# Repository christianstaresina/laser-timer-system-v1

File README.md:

# Laser Timer System

A portable two-gate laser timing system for sprint and speed training. Gate 1
(transmitter) sends a radio start event when its laser beam breaks. Gate 2
(receiver) starts and stops the timer, shows elapsed time on a 16×2 LCD, and can
display average speed from a configured distance.

v1 hardware is a **single shared PCB**. Role is selected by which v2 sketch is
flashed. There is no in-tree v1 sketch; the active firmware is v2 only.

## Repository layout

| Path | Purpose |
| --- | --- |
| `firmware/transmitter/laser_timer_v2_tx/` | Gate 1 / start-unit Arduino sketch. |
| `firmware/receiver/laser_timer_v2_rx/` | Gate 2 / finish-unit sketch (LCD menu + EEPROM). |
| `firmware/common/radio_protocol_v2.h` | Reference copy of the nRF24 packet contract. Keep in sync with each sketch-local `src/radio_protocol_v2.h`. |
| `hardware/transmitter-or-receiver/` | KiCad 8 source for the shared V1 PCB. |
| `production/transmitter-or-receiver/` | Gerbers, drills, zip, and PCBA BoM. |
| `docs/firmware-v2.md` | Firmware architecture, protocol, workflows, settings, and pitfalls. |
| `docs/hardware-production.md` | Pin map, JST harness pinouts, power tree, expansion headers, and fab artifacts. |
| `docs/Laser_Timer_Schematic.pdf` | Exported schematic. |
| `docs/Laser_Timer_PCBA.jpg` | Assembled board photo. |

Open each v2 sketch **folder** in the Arduino IDE so the adjacent `src/` files
compile with the `.ino`. Sketches include their local `src/radio_protocol_v2.h`;
`firmware/common/` is not on the compile path.

## Quick start

1. Install Arduino IDE (or CLI) with an AVR / Nano board package.
2. Install libraries: `RF24` (TMRh20), `LiquidCrystal_I2C` (plus built-in `SPI`,
   `Wire`, `EEPROM` on the receiver).
3. Board: Arduino Nano / ATmega328P (match the processor variant on the module).
4. Flash `firmware/transmitter/laser_timer_v2_tx/laser_timer_v2_tx.ino` to gate 1.
5. Flash `firmware/receiver/laser_timer_v2_rx/laser_timer_v2_rx.ino` to gate 2.

The buzzer shares Nano UART TX (`D1`). Disconnect the buzzer or expect flaky USB
uploads. Shared hardware assumptions: nRF24 CE `D9` / CSN `D10` / SPI `D11`–`D13`,
beam sensor on `D2` (active `HIGH` when broken), LCD I2C `0x27`. Receiver encoder:
button `D3`, CLK `D4`, DAT `D5`. Both sketches drive `A0` high before radio init;
the PCB maps regulator enable to `A7`. Accessories run on board `+5V` (U1); the
radio runs on board `+3V3` (U2). Those rails are **not** the Nano’s `5V` / `3V3`
pins — see [`docs/hardware-production.md`](docs/hardware-production.md).

## Operating workflow

1. Power the **receiver** first so it is listening (` Pairing...` /
   `Waiting for link`).
2. Power the transmitter. `setup()` blocks in `waitForPairing()` until
   `sendPacket(CMD_PING)` returns true, then listens for finish packets.
3. Confirm the receiver leaves pairing (it accepts **any** valid magic packet,
   not only pings). Idle **bottom** row should read `Ready`. The receiver paints
   `Link OK!` and then replaces it in the same `loop()`; it does not hold that
   screen for 1.5 s. The transmitter does, via `delay` inside `waitForPairing()`.
   The RX menu can be opened before the first packet; pairing still completes
   in the background. A finish within 1.5 s of that first packet can have its
   frozen time cleared when the receiver’s pairing timer expires.
4. On the receiver, long-press the encoder (≥ 800 ms) and select **Stopwatch**
   to arm. The handler paints `Starting...`. The next `loop()` replaces it
   with the live time if a count is running, otherwise with the idle screen
   (pairing text if no packet has arrived, else `Ready`, `Align laser`, or
   `No TX signal`). The 300 ms toast flag does not keep that text up. Arming
   is **RAM-only** — a receiver power cycle returns to disarmed even though
   Speed / distance / buzzer persist in EEPROM. Speed print-on-finish defaults
   **ON** (40 yd).
5. Break gate 1 only after that arm. TX latches `Timer counting` /
   `Waiting gate 2` on every rising edge, armed or not. If the receiver was
   still disarmed, it does not start the clock, and once the beam restores the
   transmitter sends nothing further. About 2 s later the receiver bottom row
   is `No TX signal` while TX still says `Timer counting`. Power-cycle TX, or
   arm and finish a later crossing. An armed break bursts `CMD_GATE1_OPEN`;
   RX starts the seconds display on the **top** row.
6. Break gate 2 (a **new** beam-break while counting) → RX freezes time,
   optionally prints speed, sends `CMD_GATE2_CLOSED`, shows `Finished`. TX shows
   `Timer complete!` then returns to idle art. RX stays **armed** for the next
   start packet until it is power-cycled.

A second gate-1 break while RX is already counting does **not** restart the
clock. If the finish beam is already broken when the start packet arrives, the
clock starts but will not stop until the beam restores and breaks again. If the
**start** beam is still broken when the finish packet is sent, the transmitter
is still repeating `GATE1_OPEN`, and the receiver can start a new count
immediately because it stays armed.

There is no serial console; status is LCD text only. Gate inputs float (no
pull-up, no debounce). `Align laser` can appear while the receiver is disarmed;
the align beep runs only after Stopwatch is armed. Menu confirmations are
redrawn over in the select handler. `Starting...` is replaced on the next
loop as well (live time if counting, otherwise idle). The 300 ms flag still
ignores in-menu encoder input, and when it expires it blanks the top row
during a count or a `Finished` display. Holding the button after a menu press
stalls the receiver loop until release. If an align or finish beep's timer
expires during that hold, `tone()` keeps running until the next
`handleRxBuzzer()` after release. A long-press leaves Main, Speed,
Radio, and Buzzer; on the custom distance editor it does nothing (a short
press is the only exit, and it saves). Protocol, menu tree, and
source-verified constraints:
[`docs/firmware-v2.md`](docs/firmware-v2.md).

## Hardware and production

One shared PCB is assembled for either role. User-facing JST pinouts (power,
LCD, encoder, sensor), expansion headers, and manufacturing outputs live under
[`docs/hardware-production.md`](docs/hardware-production.md) and
`production/transmitter-or-receiver/`. Read that hardware note before board
spins, harness builds, or pin changes.

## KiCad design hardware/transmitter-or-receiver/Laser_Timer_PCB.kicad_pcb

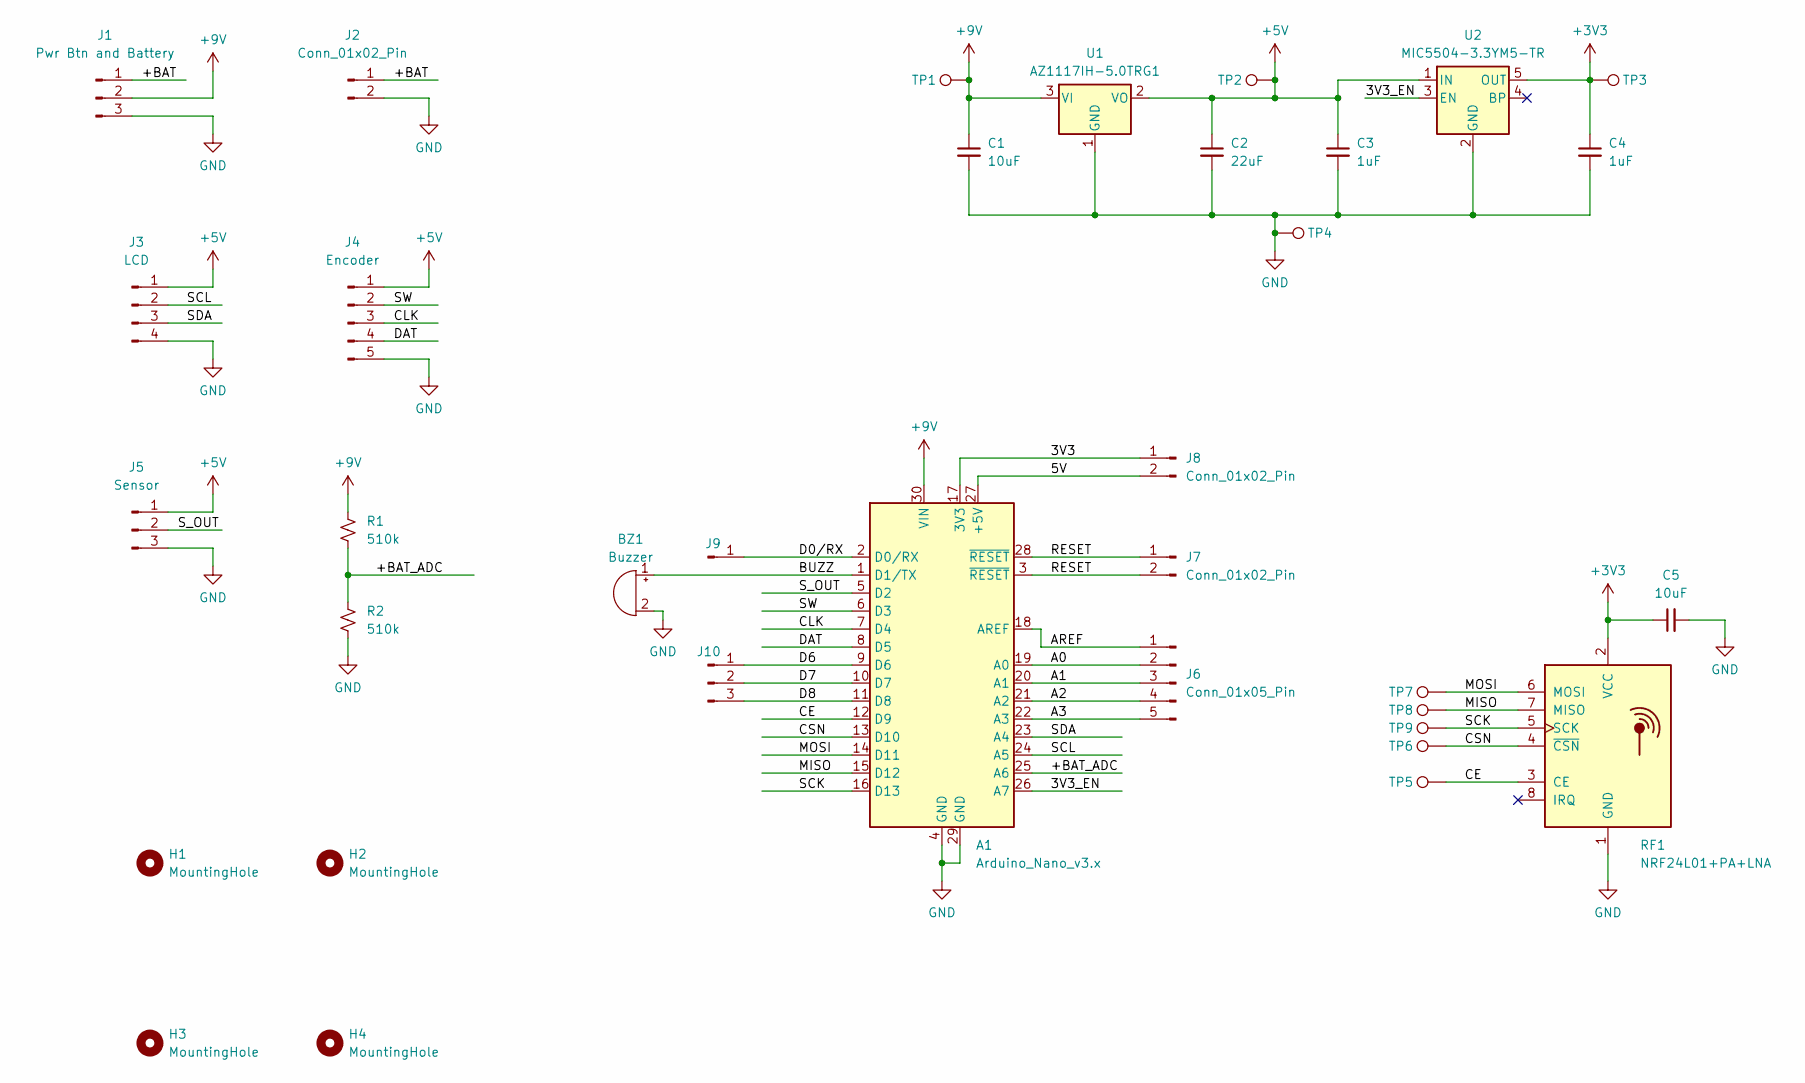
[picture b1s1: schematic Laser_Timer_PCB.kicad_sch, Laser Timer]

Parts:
A1: Arduino_Nano_v3.x; Arduino_Nano
BZ1: Buzzer; Buzzer_TDK_PS1240P02BT_D12.2mm_H6.5mm
C1, C5: 10uF; C_0805_2012Metric_Pad1.18x1.45mm_HandSolder
C2: 22uF; C_0805_2012Metric_Pad1.18x1.45mm_HandSolder
C3, C4: 1uF; C_0603_1608Metric_Pad1.08x0.95mm_HandSolder
H1, H2, H3, H4: MountingHole; MountingHole_3.2mm_M3
J1: Pwr Btn and Battery; JST_EH_B3B-EH-A_1x03_P2.50mm_Vertical
J2: Conn_01x02_Pin; JST_EH_B2B-EH-A_1x02_P2.50mm_Vertical
J3: LCD; JST_EH_B4B-EH-A_1x04_P2.50mm_Vertical
J4: Encoder; JST_EH_B5B-EH-A_1x05_P2.50mm_Vertical
J5: Sensor; JST_EH_B3B-EH-A_1x03_P2.50mm_Vertical
J6: Conn_01x05_Pin; PinHeader_1x05_P2.54mm_Vertical
J7, J8: Conn_01x02_Pin; PinHeader_1x02_P2.54mm_Vertical
J9: Conn_01x01_Pin; PinHeader_1x01_P2.54mm_Vertical
J10: Conn_01x03_Pin; PinHeader_1x03_P2.54mm_Vertical
R1, R2: 510k; R_0603_1608Metric_Pad0.98x0.95mm_HandSolder
RF1: NRF24L01+PA+LNA; nRF24L01+PA+LNA
TP1, TP2, TP3, TP4, TP5, TP6, TP7, TP8, TP9: TestPoint; TestPoint_Pad_D1.0mm
U1: AZ1117IH-5.0TRG1; SOT-223-3_TabPin2
U2: MIC5504-3.3YM5-TR; SOT-23-5

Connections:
+3V3: C4.1, C5.1, RF1.2 (VCC), TP3.1, U2.5 (OUT)
+5V: C2.1, C3.1, J3.1, J4.1, J5.1, TP2.1, U1.2 (VO), U2.1 (IN)
+9V: A1.30 (VIN), C1.1, J1.2, R1.1, TP1.1, U1.3 (VI)
/3V3: A1.17 (3V3), J8.1
/3V3_EN: A1.26 (A7), U2.3 (EN)
/5V: A1.27 (+5V), J8.2
/+BAT: J1.1, J2.1
/+BAT_ADC: A1.25 (A6), R1.2, R2.1
/A0: A1.19 (A0), J6.2
/A1: A1.20 (A1), J6.3
/A2: A1.21 (A2), J6.4
/A3: A1.22 (A3), J6.5
/AREF: A1.18 (AREF), J6.1
/BUZZ: A1.1 (D1/TX), BZ1.1 (+)
/CE: A1.12 (D9), RF1.3 (CE), TP5.1
/CLK: A1.7 (D4), J4.3
/CSN: A1.13 (D10), RF1.4 (~CSN), TP6.1
/D0/RX: A1.2 (D0/RX), J9.1
/D6: A1.9 (D6), J10.1
/D7: A1.10 (D7), J10.2
/D8: A1.11 (D8), J10.3
/DAT: A1.8 (D5), J4.4
/MISO: A1.15 (D12), RF1.7 (MISO), TP8.1
/MOSI: A1.14 (D11), RF1.6 (MOSI), TP7.1
/RESET: A1.3 (~RESET), A1.28 (~RESET), J7.1, J7.2
/SCK: A1.16 (D13), RF1.5 (SCK), TP9.1
/SCL: A1.24 (A5), J3.2
/SDA: A1.23 (A4), J3.3
/SW: A1.6 (D3), J4.2
/S_OUT: A1.5 (D2), J5.2
GND: A1.4 (GND), A1.29 (GND), BZ1.2 (-), C1.2, C2.2, C3.2, C4.2, C5.2, J1.3, J2.2, J3.4, J4.5, J5.3, R2.2, RF1.1 (GND), TP4.1, U1.1 (GND), U2.2 (GND)

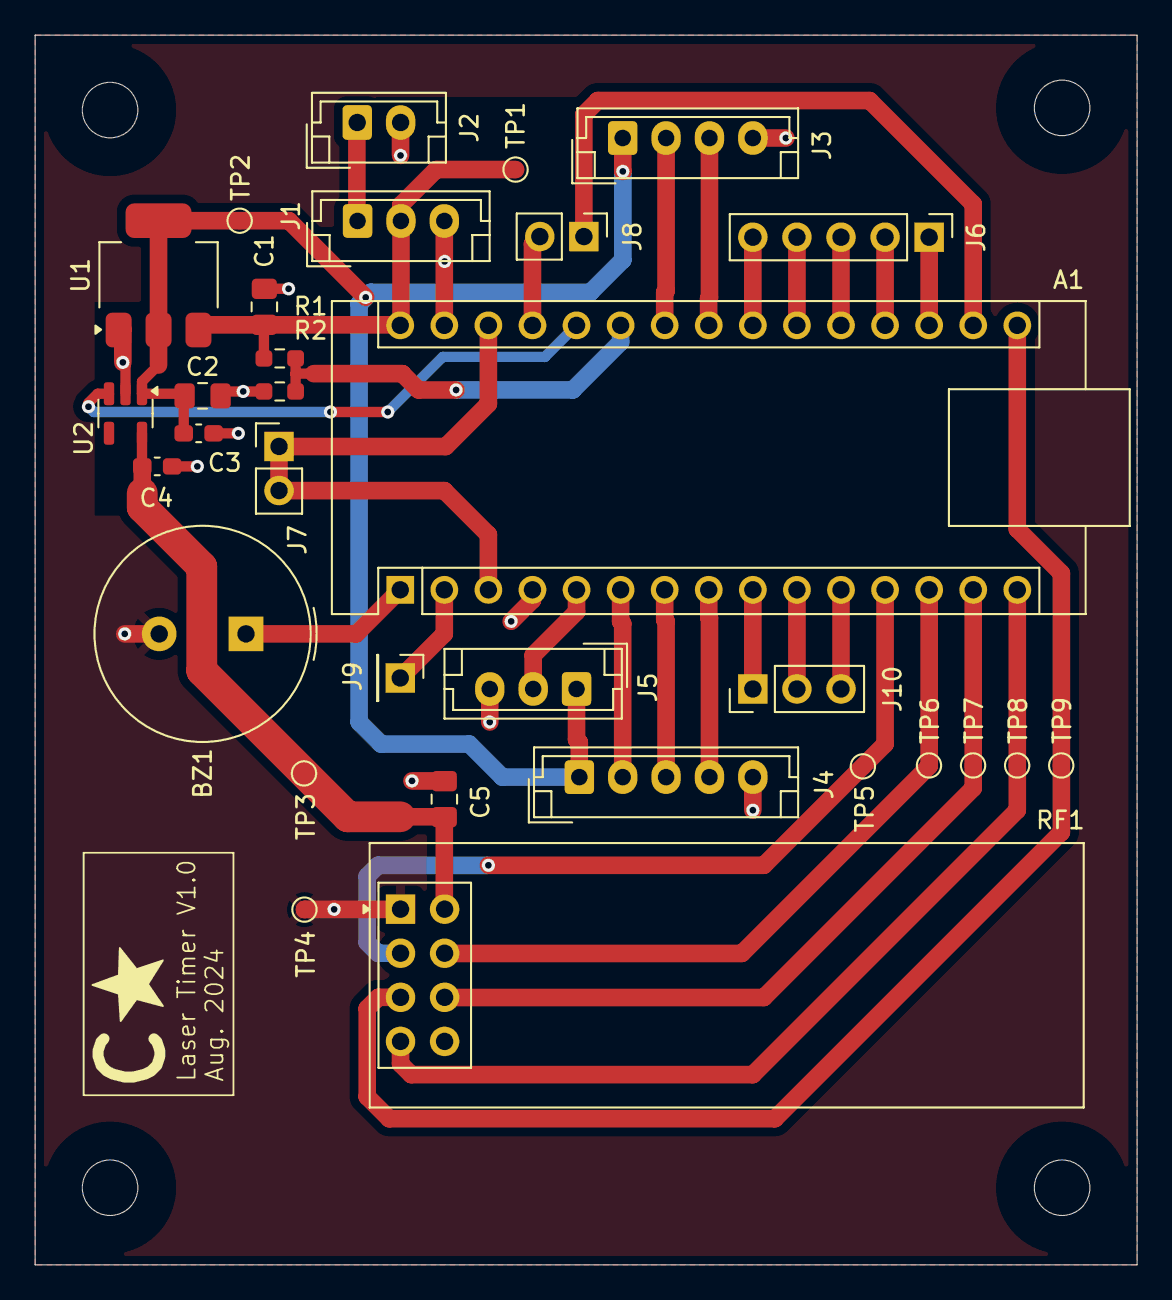
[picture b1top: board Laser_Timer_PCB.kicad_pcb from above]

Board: 2 copper layers, 63.5 x 70.9 mm, 35 parts (0 on the bottom side), 31 nets.

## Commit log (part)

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2026-05-30 Add archived project files
    Transfers archived local copy of all the project files to GitHub for the first time. Most recent firmware changes were made in August 2024.
2026-05-30 Clean up README.md by removing unnecessary blank lines
    Removed extra blank lines for improved readability.
2026-06-08 Document firmware v2 setup and operation
2026-06-08 Fix receiver re-pair radio packet detection
2026-06-08 Add RX re-pair regression test
2026-06-08 Use unittest for RX re-pair regression test
2026-06-08 Stub Wire in RX re-pair test
2026-06-15 Document laser timer firmware v2
2026-06-15 Fix blocking timer and re-pair firmware paths
2026-06-15 Keep transmitter loop live during encoder hold
2026-06-22 Document firmware v2 workflows
2026-06-22 Fix timer run-state and encoder blocking bugs
2026-06-29 Document firmware v2 engineering workflow
